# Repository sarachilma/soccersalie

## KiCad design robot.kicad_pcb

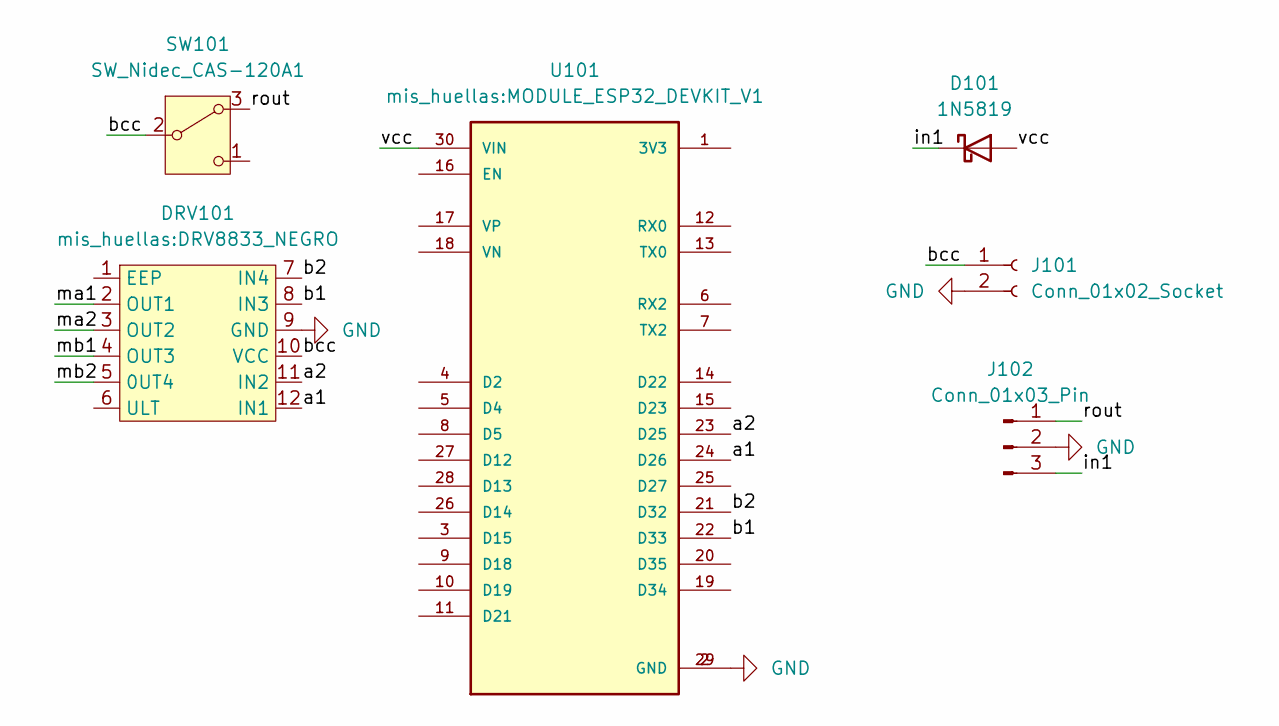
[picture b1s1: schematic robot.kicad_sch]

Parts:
D101: 1N5819; D_DO-41_SOD81_P10.16mm_Horizontal
DRV101: mis_huellas:DRV8833_NEGRO; DRV8833_NEGRO
J101: Conn_01x02_Socket; PinHeader_1x02_P2.54mm_Vertical
J102: Conn_01x03_Pin; PinHeader_1x03_P2.54mm_Vertical
SW101: SW_Nidec_CAS-120A1; Nidec_Copal_CAS-120A
U101: mis_huellas:MODULE_ESP32_DEVKIT_V1; MODULE_ESP32_DEVKIT_V1; PARTREV N/A

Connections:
/a1: DRV101.12 (IN1), U101.24 (D26)
/a2: DRV101.11 (IN2), U101.23 (D25)
/b1: DRV101.8 (IN3), U101.22 (D33)
/b2: DRV101.7 (IN4), U101.21 (D32)
/bcc: DRV101.10 (VCC), J101.1, SW101.2 (B)
/in1: D101.1 (K), J102.3
/ma1: DRV101.2 (OUT1)
/ma2: DRV101.3 (OUT2)
/mb1: DRV101.4 (OUT3)
/mb2: DRV101.5 (0UT4)
/rout: J102.1, SW101.3 (A)
/vcc: D101.2 (A), U101.30 (VIN)
GND: DRV101.9 (GND), J101.2, J102.2, U101.2 (GND), U101.29 (GND)

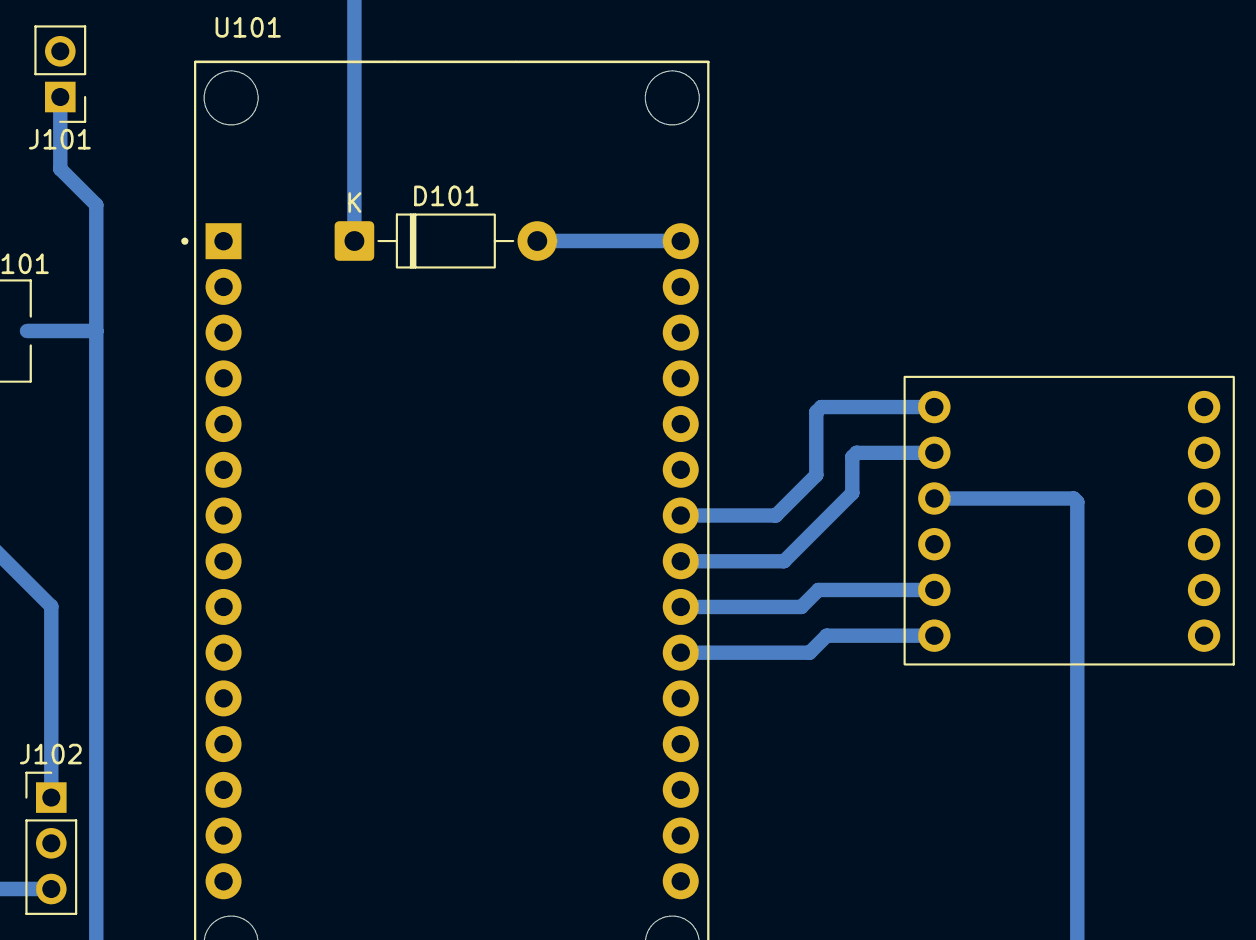
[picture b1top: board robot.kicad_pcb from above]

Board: 2 copper layers, 6 parts (0 on the bottom side), 9 nets.
